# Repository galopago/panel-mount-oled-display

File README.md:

# Panel-mount OLED display — PCB sources

Open-source KiCad designs for a two-board stack that drives a bare 0.96" I2C OLED (128×64) with screw terminals. The boards are meant to fit a 48×29 mm panel-mount enclosure; this repository contains the PCB sources and Gerbers only.

**Full project guide** (assembly, enclosure, BOM with buy links, practical notes):  
[Panel-mount 0.96" bare OLED with screw terminals](https://galopago.github.io/english/panel-mount-oled-display-en/)

## Two-board design

| Board | Folder | Role |
|-------|--------|------|
| Display board | [`display-board/`](display-board/) | Bare OLED flex (handsoldering footprint), XC6206 3.3 V LDO, auto-reset network, I2C coupling, six 0805 indicator LEDs with independent anode/cathode terminals, 1×8 header to the connector board |
| Connector board | [`connector-board/`](connector-board/) | Double-level 2×8 screw terminals (3.5 mm pitch); routes signals to the field wiring |

The stack is joined with 1×8 pin headers and a spacer so the terminals stay reachable from the side.

## Schematic

## Photos

## Repository layout

```
display-board/          KiCad project (.kicad_pro, .kicad_sch, .kicad_pcb)
connector-board/        KiCad project
library/                Custom terminal-block footprints
assets/pdf/             Component and OLED datasheets
assets/img/             Schematic and board photos
```

Gerber archives are under each board folder:

- `*/gerber/single/*.zip` — single-board fabrication
- `*/gerber/panel/*.zip` — panel fabrication

## Ordering PCBs

Upload the Gerber ZIP of your choice to your PCB fab:

| Board | Single | Panel |
|-------|--------|-------|
| Display | [`display-board-single.zip`](display-board/gerber/single/panel-mount-oled-display-display-board-single.zip) | [`display-board-panel.zip`](display-board/gerber/panel/panel-mount-oled-display-display-board-panel.zip) |
| Connector | [`connector-board-single.zip`](connector-board/gerber/single/panel-mount-oled-display-connector-board-single.zip) | [`connector-board-panel.zip`](connector-board/gerber/panel/panel-mount-oled-display-connector-board-panel.zip) |

Panel Gerbers are kept within a **100 mm × 100 mm** outline. That size fits the low-cost tier offered by many PCB fabs, so panel orders tend to stay inexpensive even when you need several boards at once.

## Opening in KiCad

Open each `.kicad_pro` file separately (KiCad 7 or newer). The local footprint library in [`library/`](library/) is referenced by the projects.

## Host interface

No on-board firmware. Any host with I2C (Arduino, ESP32, Raspberry Pi Pico, etc.) can drive the SSD1306-compatible display. Wire VCC, GND, SCL, and SDA to the screw terminals; route the six LED pairs to status signals as needed. I2C address selection is configurable on the display board (see schematic).

## What is not in this repo

Enclosure sourcing, step-by-step assembly, and the full bill of materials with purchase links are covered in the [project article](https://galopago.github.io/english/panel-mount-oled-display-en/) linked above.

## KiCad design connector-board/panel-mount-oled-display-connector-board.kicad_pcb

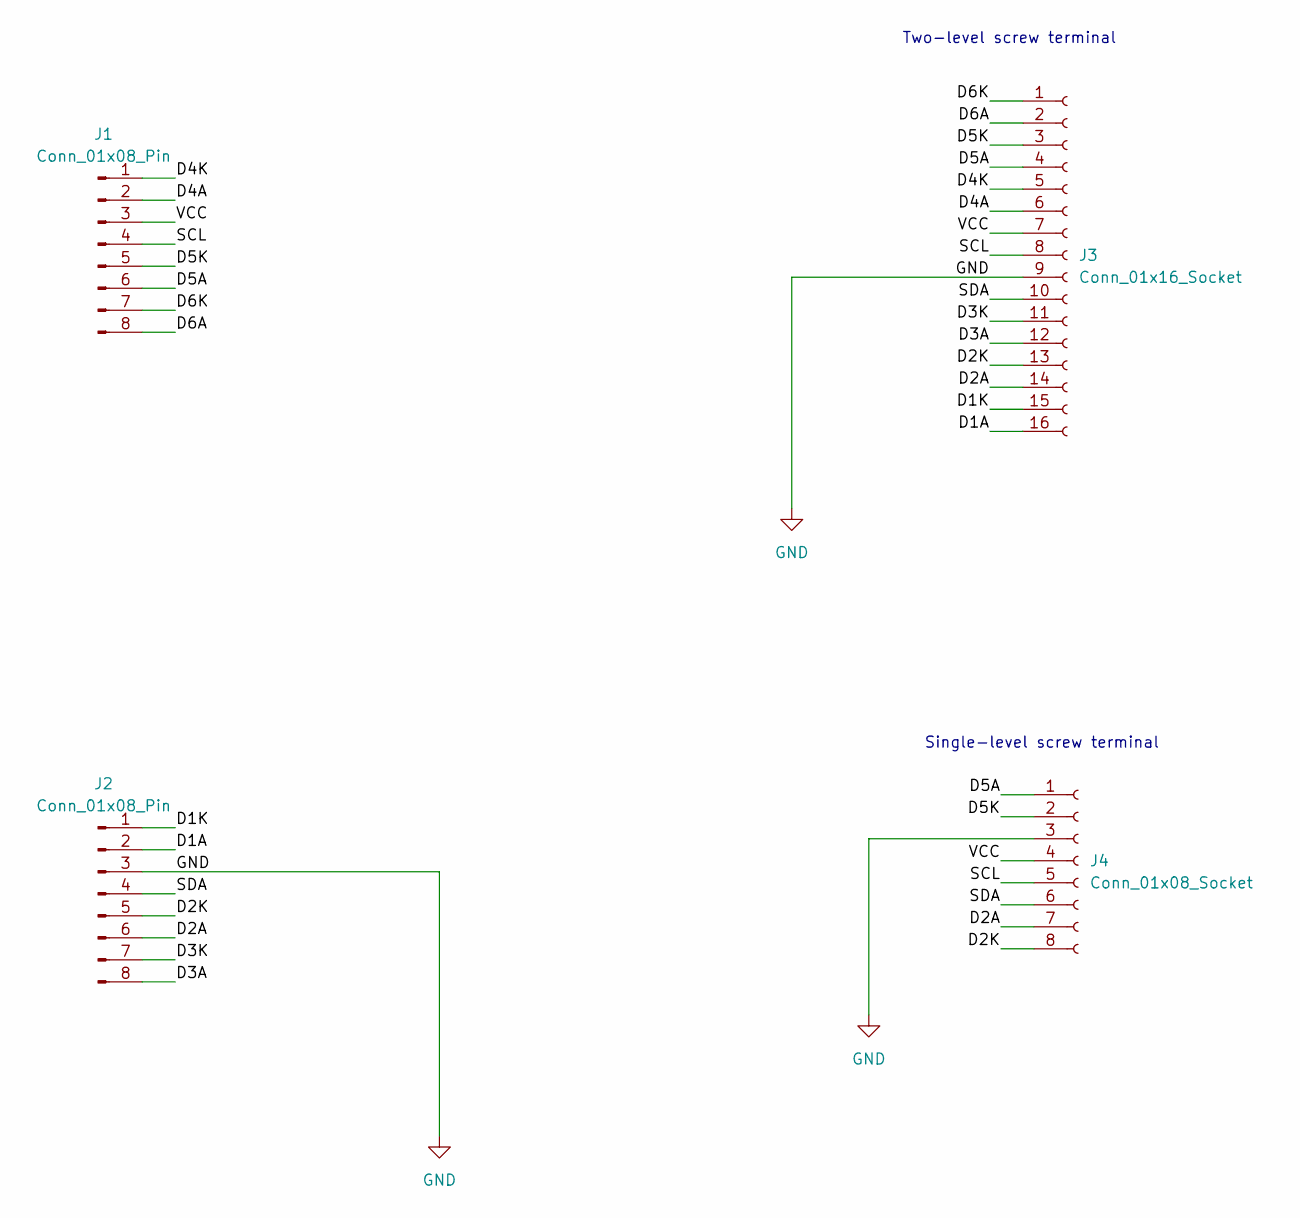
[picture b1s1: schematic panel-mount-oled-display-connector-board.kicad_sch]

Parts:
J1, J2: Conn_01x08_Pin; PinHeader_1x08_P2.54mm_Vertical
J3: Conn_01x16_Socket; TerminalBlock_DoubleLevel_2x08_P3.50mm_Horizontal
J4: Conn_01x08_Socket; TerminalBlock_4Ucon_1x08_P3.50mm_Horizontal

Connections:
/D1A: J2.2, J3.16
/D1K: J2.1, J3.15
/D2A: J2.6, J3.14, J4.7
/D2K: J2.5, J3.13, J4.8
/D3A: J2.8, J3.12
/D3K: J2.7, J3.11
/D4A: J1.2, J3.6
/D4K: J1.1, J3.5
/D5A: J1.6, J3.4, J4.1
/D5K: J1.5, J3.3, J4.2
/D6A: J1.8, J3.2
/D6K: J1.7, J3.1
/SCL: J1.4, J3.8, J4.5
/SDA: J2.4, J3.10, J4.6
/VCC: J1.3, J3.7, J4.4
GND: J2.3, J3.9, J4.3

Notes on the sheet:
Single-level screw terminal
Two-level screw terminal

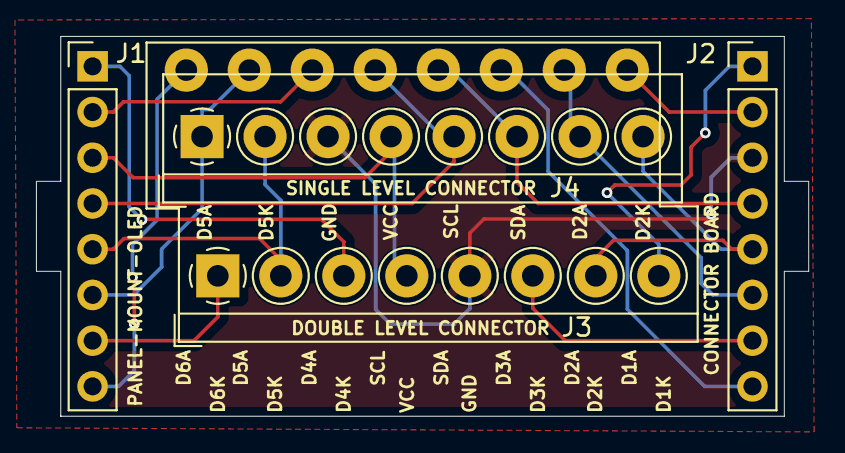
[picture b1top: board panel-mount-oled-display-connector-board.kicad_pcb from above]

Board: 2 copper layers, 42.9 x 21.1 mm, 4 parts (0 on the bottom side), 16 nets.

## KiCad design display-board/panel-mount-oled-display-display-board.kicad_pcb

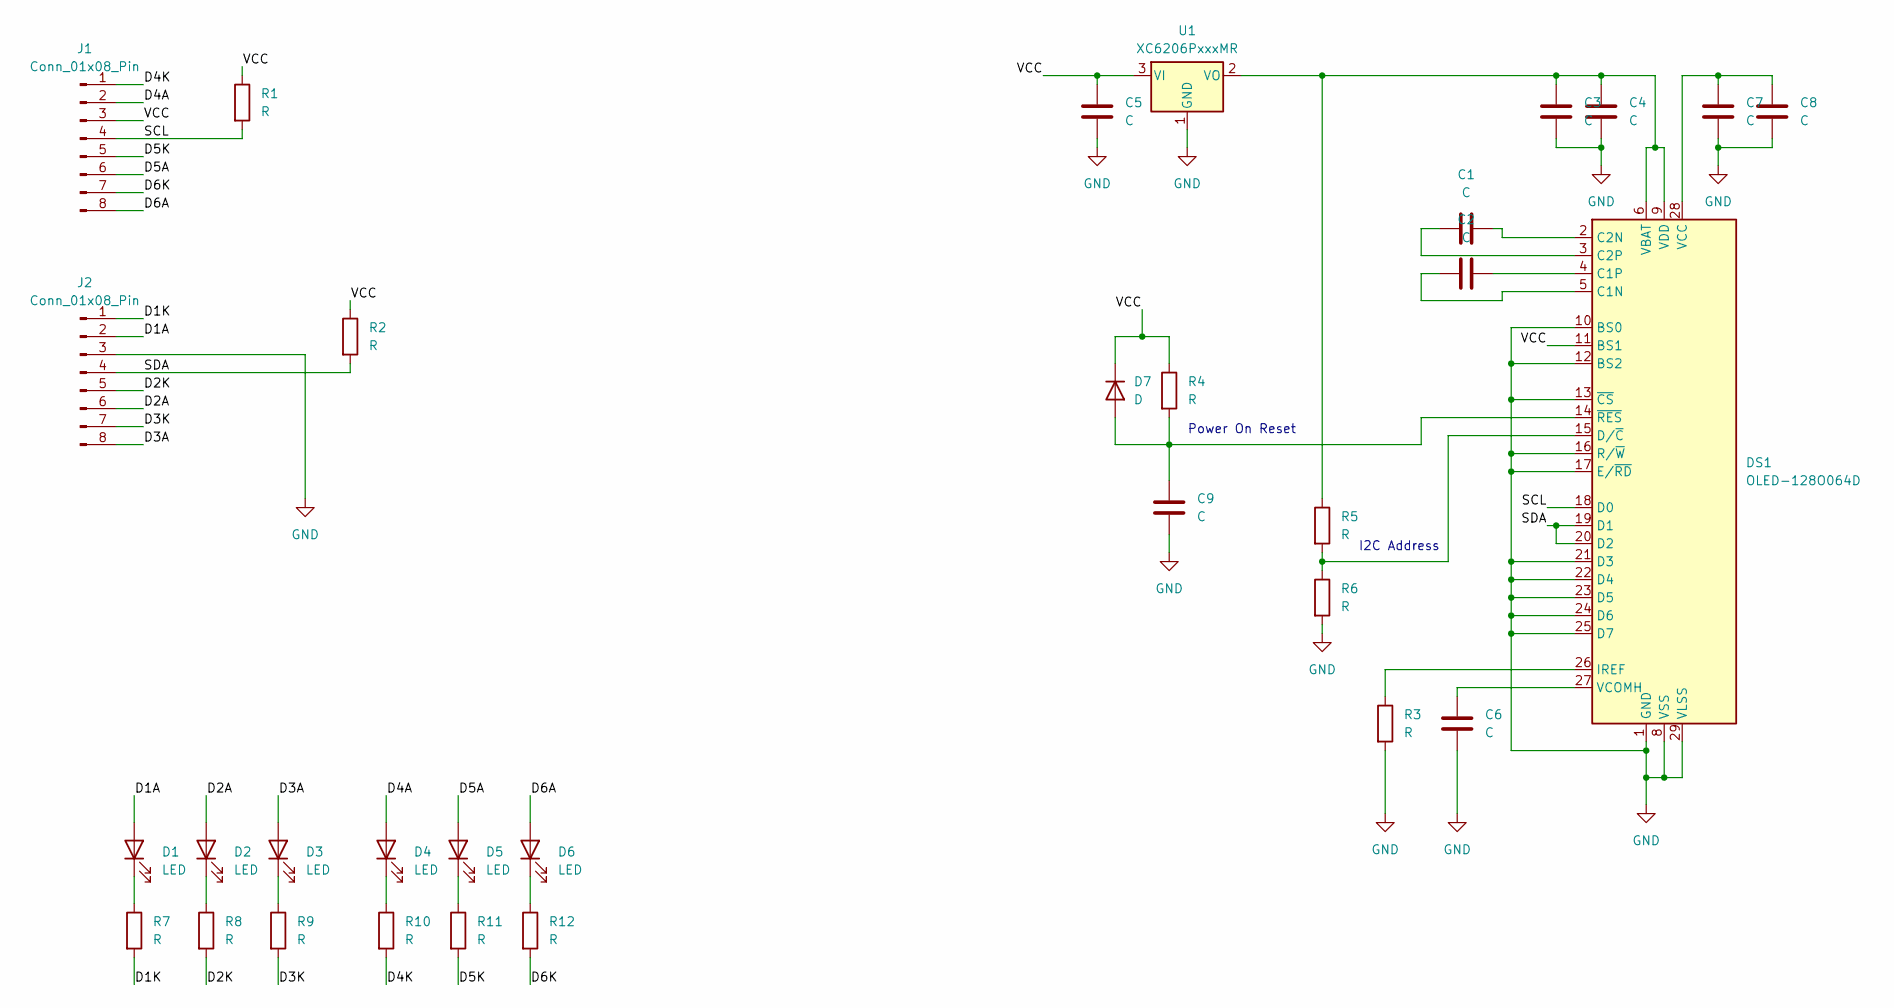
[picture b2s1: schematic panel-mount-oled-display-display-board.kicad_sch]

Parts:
C1, C2, C3, C4, C5, C6, C7, C8, C9: C; C_0805_2012Metric_Pad1.18x1.45mm_HandSolder
D1, D2, D3, D4, D5, D6: LED; LED_0805_2012Metric_Pad1.15x1.40mm_HandSolder
D7: D; D_MiniMELF_Handsoldering
DS1: OLED-128O064D; OLED-128O064D_Handsoldering
J1, J2: Conn_01x08_Pin; PinHeader_1x08_P2.54mm_Vertical
R1, R2, R3, R4, R5, R6, R7, R8, R9, R10, R11, R12: R; R_0805_2012Metric_Pad1.20x1.40mm_HandSolder
U1: XC6206PxxxMR; SOT-23-3

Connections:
/D1A: D1.2 (A), J2.2
/D1K: J2.1, R7.2
/D2A: D2.2 (A), J2.6
/D2K: J2.5, R8.2
/D3A: D3.2 (A), J2.8
/D3K: J2.7, R9.2
/D4A: D4.2 (A), J1.2
/D4K: J1.1, R10.2
/D5A: D5.2 (A), J1.6
/D5K: J1.5, R11.2
/D6A: D6.2 (A), J1.8
/D6K: J1.7, R12.2
/SCL: DS1.18 (D0), J1.4, R1.2
/SDA: DS1.19 (D1), DS1.20 (D2), J2.4, R2.2
/VCC: C5.2, D7.1 (K), DS1.11 (BS1), J1.3, R1.1, R2.1, R4.1, U1.3 (VI)
GND: C3.1, C4.1, C5.1, C6.1, C7.1, C8.1, C9.1, DS1.1 (GND), DS1.8 (VSS), DS1.10 (BS0), DS1.12 (BS2), DS1.13 (~CS), DS1.16 (R/~W), DS1.17 (E/~RD), DS1.21 (D3), DS1.22 (D4), DS1.23 (D5), DS1.24 (D6), DS1.25 (D7), DS1.29 (VLSS), DS1.30 (GND), J2.3, R3.2, R6.2, U1.1 (GND)
unnamed: D1.1 (K), R7.1
unnamed: D2.1 (K), R8.1
unnamed: D3.1 (K), R9.1
unnamed: D4.1 (K), R10.1
unnamed: D5.1 (K), R11.1
unnamed: D6.1 (K), R12.1
unnamed: C9.2, D7.2 (A), DS1.14 (~RES), R4.2
unnamed: C2.2, DS1.5 (C1N)
unnamed: C2.1, DS1.4 (C1P)
unnamed: C1.1, DS1.2 (C2N)
unnamed: C1.2, DS1.3 (C2P)
unnamed: DS1.15 (D/~C), R5.2, R6.1
unnamed: DS1.26 (IREF), R3.1
unnamed: C3.2, C4.2, DS1.6 (VBAT), DS1.9 (VDD), R5.1, U1.2 (VO)
unnamed: C7.2, C8.2, DS1.28 (VCC)
unnamed: C6.2, DS1.27 (VCOMH)

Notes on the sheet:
I2C Address
Power On Reset

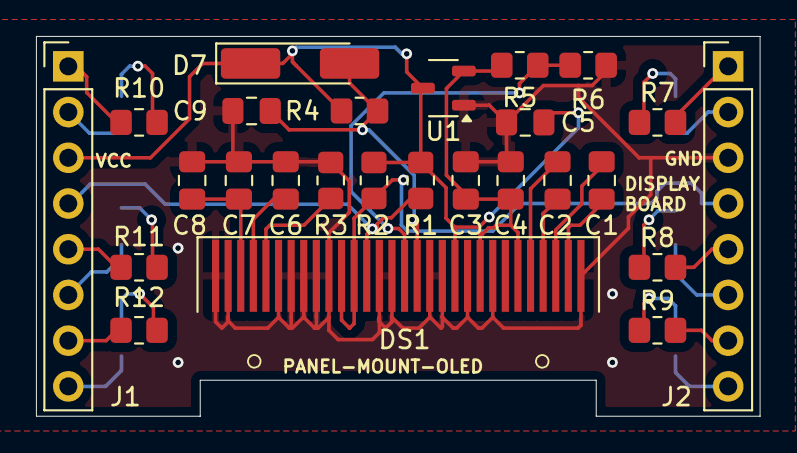
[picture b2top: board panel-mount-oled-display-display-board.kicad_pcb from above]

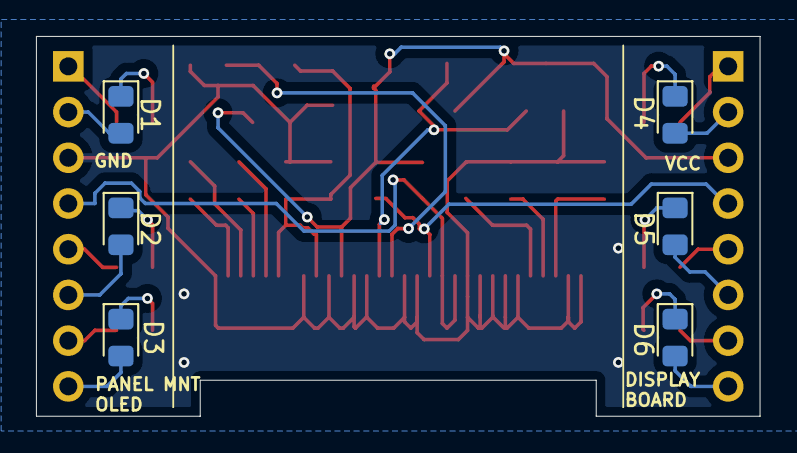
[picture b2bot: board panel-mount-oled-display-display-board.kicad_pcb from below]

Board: 2 copper layers, 40.2 x 21.1 mm, 32 parts (6 on the bottom side), 32 nets.

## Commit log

2026-03-01 Initial commit: KiCad project panel-mount-oled-display
2026-05-07 Restructure repository into connector-board, display-board, and shared library
    - Replace flat root KiCad project with split connector-board and display-board projects
    - Add shared TerminalBlock_DoubleLevel footprints under library/
    - Include gerber exports (single and panel), fabrication archives, and KiCad backups
2026-05-09 display: OLED handsolder footprint, schematic/PCB update, datasheets and backups
    - Assign Display_Handsoldering OLED-128O064D_Handsoldering footprint and refresh board
    - Update fp-lib-table and fp-info-cache
    - Add datasheet PDFs, project backup zips, remove superseded connector backup
2026-05-11 Expand display board schematic with additional components
    Update KiCad schematic and PCB to reflect new circuitry. Refresh
    project backup archives and remove superseded backup snapshot.
2026-05-11 display: finish board routing and checkpoint KiCad outputs
    Capture the fully routed display board together with the generated KiCad
    artifacts and fresh backups for this layout milestone.
2026-05-11 display: add single-board Gerber fabrication files
    Generate Gerber and drill outputs for a single display board, update the
    KiCad plot settings to export into gerber/single, and checkpoint the
    matching fabrication archive and refreshed backup.
2026-05-11 display: add panel Gerber fabrication files
    Generate the panelized Gerber and drill outputs for the display board,
    archive the fabrication bundle, and checkpoint the latest KiCad backups.
2026-06-07 display: widen PCB cutout and reposition LEDs clear of bezel
    Expand the display mounting area slightly to fit marginally wider
    OLED modules, and shift the status LEDs so they are not obstructed
    by the panel bezel.
2026-06-07 display: regenerate single-board Gerber fabrication files
    Export updated Gerber and drill outputs for a single display board
    from the latest PCB layout.
2026-06-07 display: update KiCad project backup
    Rotate display board KiCad backup after regenerating single-board
    Gerber fabrication files.
2026-06-07 display: regenerate panel Gerber fabrication files
    Export panelized Gerber and drill outputs for production fabrication
    of the display board from the latest PCB layout.
2026-06-08 connector: add dual screw-terminal connector options
    Add a new connector on the connector board to support either
    single-level or two-level screw terminal blocks, providing
    flexibility to expose more LEDs when needed.
2026-06-08 display: update KiCad project backup
    Rotate display board KiCad backup after connector board schematic
    and layout updates.
2026-06-08 connector: regenerate single-board Gerber fabrication files
    Export Gerber and drill outputs for a single connector board from
    the latest PCB layout.
2026-06-08 connector: update KiCad project backup
    Rotate connector board KiCad backup after regenerating single-board
    Gerber fabrication files.
2026-06-08 connector: regenerate panel Gerber fabrication files
    Export panelized Gerber and drill outputs for production fabrication
    of the connector board from the latest PCB layout.
2026-06-17 Add PCB-focused README with optimized board images.
    Document the two-board KiCad design and Gerber locations, and add web-friendly photos plus a resized schematic for GitHub.
2026-06-17 Note 100 mm panel Gerber limit in README.
    Clarify that panel outlines stay within 100 mm × 100 mm to qualify for low-cost PCB fab tiers.
2026-06-17 Update KiCad project backups for display and connector boards.
    Replace the outdated display-board archive and add the latest connector-board backup.
